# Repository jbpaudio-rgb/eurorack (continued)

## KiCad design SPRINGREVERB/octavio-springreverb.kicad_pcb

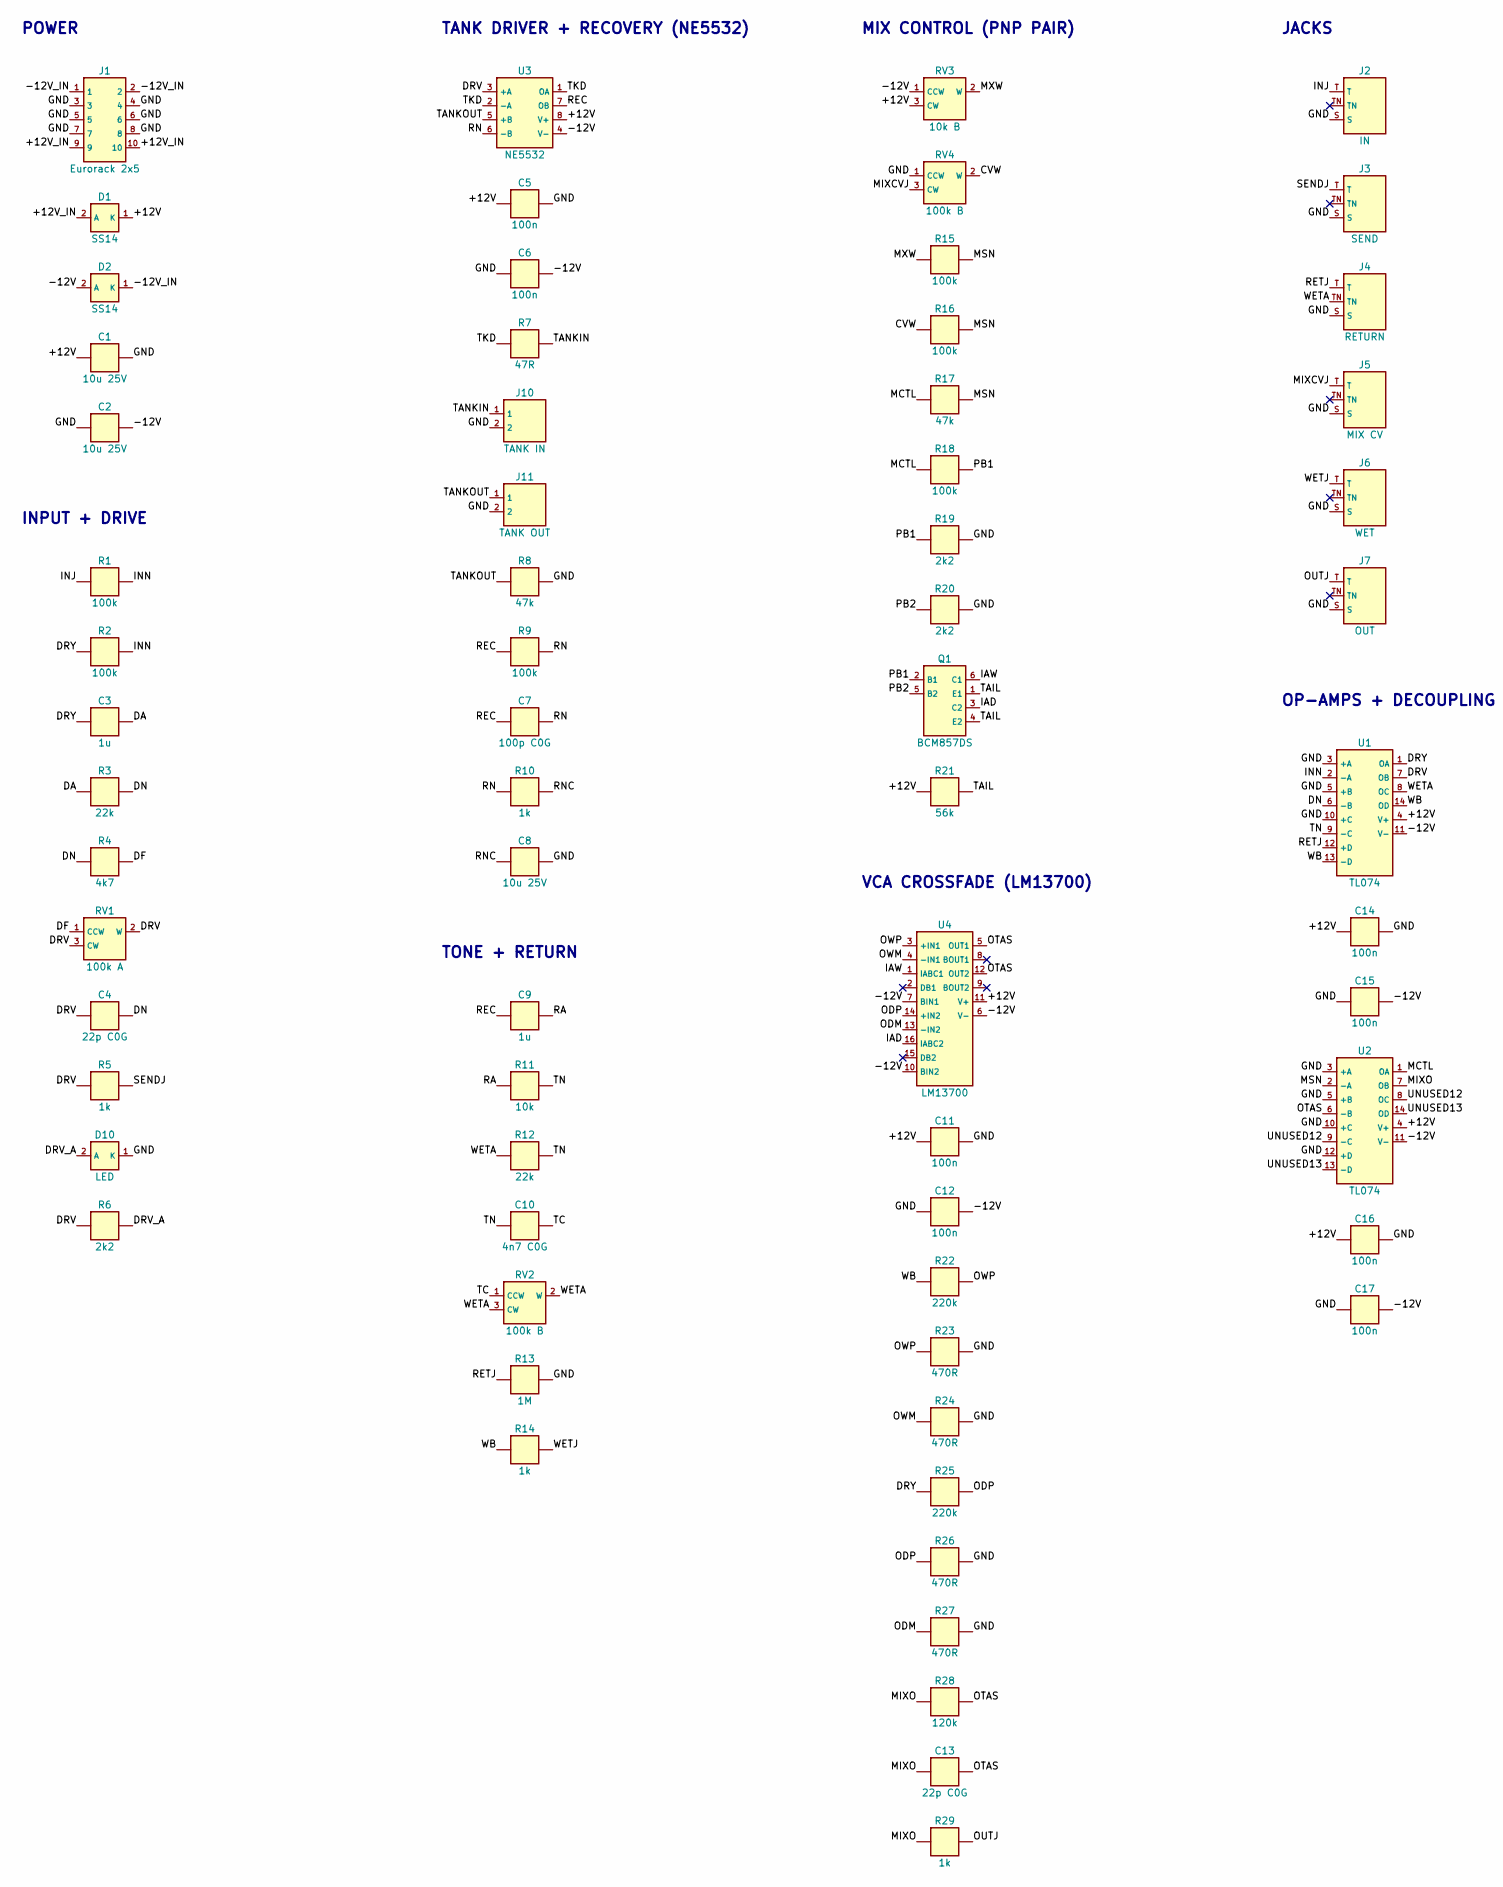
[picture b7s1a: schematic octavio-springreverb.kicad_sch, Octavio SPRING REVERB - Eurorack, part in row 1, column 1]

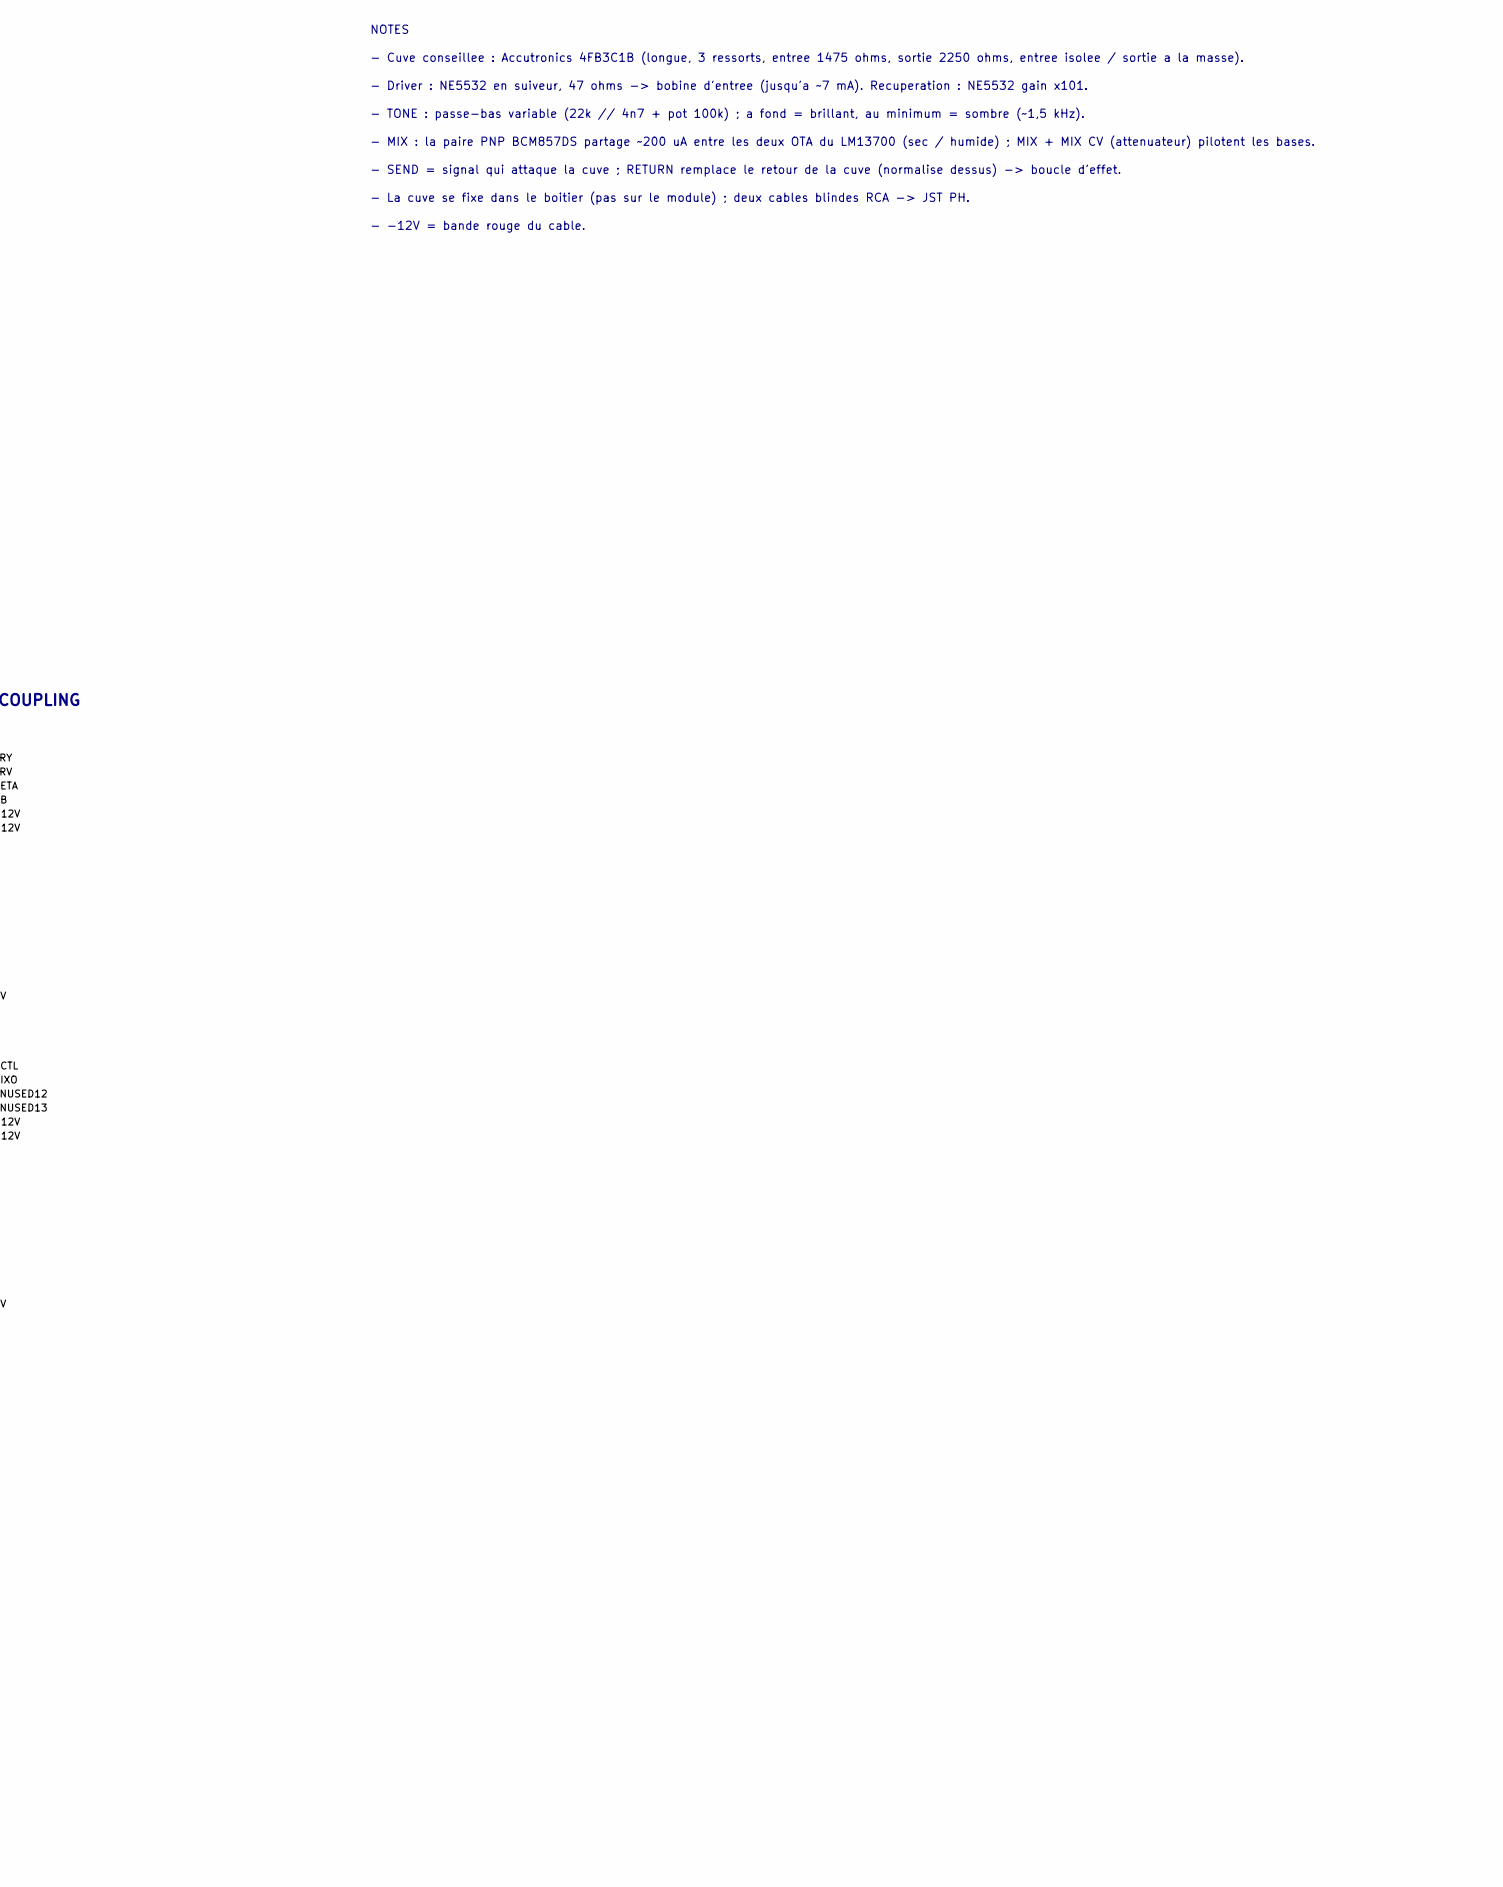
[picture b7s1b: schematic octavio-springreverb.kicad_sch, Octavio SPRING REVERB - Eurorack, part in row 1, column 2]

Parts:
C1, C2, C8: 10u 25V; C_1206_3216Metric; MPN X5R/X7R 1206
C3, C9: 1u; C_0603_1608Metric; MPN X7R 0603 25 V
C4, C13: 22p C0G; C_0603_1608Metric; MPN C0G/NP0 0603
C5, C6, C11, C12, C14, C15, C16, C17: 100n; C_0603_1608Metric
C7: 100p C0G; C_0603_1608Metric; MPN C0G/NP0 0603
C10: 4n7 C0G; C_0603_1608Metric; MPN C0G/NP0 0603
D1, D2: SS14; D_SMA; MPN SS14 (40 V 1 A Schottky)
D10: LED; LED_D3.0mm; MPN LED 3 mm rouge (PEAK : s'allume quand l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
J1: Eurorack 2x5; IDC-Header_2x05_P2.54mm_Vertical; MPN Shrouded header 2x5 2.54 mm
J2: IN; Jack_3.5mm_Thonkiconn_PJ398SM; MPN QingPu WQP-PJ301M-12 (Thonkiconn)
J3: SEND; Jack_3.5mm_Thonkiconn_PJ398SM; MPN QingPu WQP-PJ301M-12 (Thonkiconn)
J4: RETURN; Jack_3.5mm_Thonkiconn_PJ398SM; MPN QingPu WQP-PJ301M-12 (Thonkiconn)
J5: MIX CV; Jack_3.5mm_Thonkiconn_PJ398SM; MPN QingPu WQP-PJ301M-12 (Thonkiconn)
J6: WET; Jack_3.5mm_Thonkiconn_PJ398SM; MPN QingPu WQP-PJ301M-12 (Thonkiconn)
J7: OUT; Jack_3.5mm_Thonkiconn_PJ398SM; MPN QingPu WQP-PJ301M-12 (Thonkiconn)
J10: TANK IN; JST_PH_B2B-PH-K_1x02_P2.00mm_Vertical; MPN JST PH 2 broches (câble blindé vers la 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
J11: TANK OUT; JST_PH_B2B-PH-K_1x02_P2.00mm_Vertical; MPN JST PH 2 broches (câble blindé vers la 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
Q1: BCM857DS; SOT-457; MPN BCM857DS,115 (Nexperia, paire PNP appai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
R1, R2, R9, R15, R16, R18: 100k; R_0603_1608Metric
R3, R12: 22k; R_0603_1608Metric
R4: 4k7; R_0603_1608Metric
R5, R10, R14, R29: 1k; R_0603_1608Metric
R6, R19, R20: 2k2; R_0603_1608Metric
R7: 47R; R_0603_1608Metric
R8, R17: 47k; R_0603_1608Metric
R11: 10k; R_0603_1608Metric
R13: 1M; R_0603_1608Metric
R21: 56k; R_0603_1608Metric
R22, R25: 220k; R_0603_1608Metric
R23, R24, R26, R27: 470R; R_0603_1608Metric
R28: 120k; R_0603_1608Metric
RV1: 100k A; Pot_Alpha_9mm_Vertical; MPN POT-R09V-100K A (9 mm vertical, log)
RV2, RV4: 100k B; Pot_Alpha_9mm_Vertical; MPN POT-R09V-100K (9 mm vertical, B100k)
RV3: 10k B; Pot_Alpha_9mm_Vertical; MPN POT-R09V-10K B (9 mm vertical)
U1, U2: TL074; SOIC-14_3.9x8.7mm_P1.27mm; MPN TL074CDR
U3: NE5532; SOIC-8_3.9x4.9mm_P1.27mm; MPN NE5532DR (double ampli bas bruit, sorti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
U4: LM13700; SOIC-16_3.9x9.9mm_P1.27mm; MPN LM13700MX/NOPB

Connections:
+12V: C1.1, C5.1, C11.1, C14.1, C16.1, D1.1 (K), R21.1, RV3.3 (CW), U1.4 (V+), U2.4 (V+), U3.8 (V+), U4.11 (V+)
+12V_IN: D1.2 (A), J1.9, J1.10
-12V: C2.2, C6.2, C12.2, C15.2, C17.2, D2.2 (A), RV3.1 (CCW), U1.11 (V-), U2.11 (V-), U3.4 (V-), U4.6 (V-), U4.7 (BIN1), U4.10 (BIN2)
-12V_IN: D2.1 (K), J1.1, J1.2
CVW: R16.1, RV4.2 (W)
DA: C3.2, R3.1
DF: R4.2, RV1.1 (CCW)
DN: C4.2, R3.2, R4.1, U1.6 (-B)
DRV: C4.1, R5.1, R6.1, RV1.2 (W), RV1.3 (CW), U1.7 (OB), U3.3 (+A)
DRV_A: D10.2 (A), R6.2
DRY: C3.1, R2.1, R25.1, U1.1 (OA)
GND: C1.2, C2.1, C5.2, C6.1, C8.2, C11.2, C12.1, C14.2, C15.1, C16.2, C17.1, D10.1 (K), J1.3, J1.4, J1.5, J1.6, J1.7, J1.8, J2.S, J3.S, J4.S, J5.S, J6.S, J7.S, J10.2, J11.2, R8.2, R13.2, R19.2, R20.2, R23.2, R24.2, R26.2, R27.2, RV4.1 (CCW), U1.3 (+A), U1.5 (+B), U1.10 (+C), U2.3 (+A), U2.5 (+B), U2.10 (+C), U2.12 (+D)
IAD: Q1.3 (C2), U4.16 (IABC2)
IAW: Q1.6 (C1), U4.1 (IABC1)
INJ: J2.T, R1.1
INN: R1.2, R2.2, U1.2 (-A)
MCTL: R17.1, R18.1, U2.1 (OA)
MIXCVJ: J5.T, RV4.3 (CW)
MIXO: C13.1, R28.1, R29.1, U2.7 (OB)
MSN: R15.2, R16.2, R17.2, U2.2 (-A)
MXW: R15.1, RV3.2 (W)
ODM: R27.1, U4.13 (-IN2)
ODP: R25.2, R26.1, U4.14 (+IN2)
OTAS: C13.2, R28.2, U2.6 (-B), U4.5 (OUT1), U4.12 (OUT2)
OUTJ: J7.T, R29.2
OWM: R24.1, U4.4 (-IN1)
OWP: R22.2, R23.1, U4.3 (+IN1)
PB1: Q1.2 (B1), R18.2, R19.1
PB2: Q1.5 (B2), R20.1
RA: C9.2, R11.1
REC: C7.1, C9.1, R9.1, U3.7 (OB)
RETJ: J4.T, R13.1, U1.12 (+D)
RN: C7.2, R9.2, R10.1, U3.6 (-B)
RNC: C8.1, R10.2
SENDJ: J3.T, R5.2
TAIL: Q1.1 (E1), Q1.4 (E2), R21.2
TANKIN: J10.1, R7.2
TANKOUT: J11.1, R8.1, U3.5 (+B)
TC: C10.2, RV2.1 (CCW)
TKD: R7.1, U3.1 (OA), U3.2 (-A)
TN: C10.1, R11.2, R12.2, U1.9 (-C)
UNUSED12: U2.8 (OC), U2.9 (-C)
UNUSED13: U2.13 (-D), U2.14 (OD)
WB: R14.1, R22.1, U1.13 (-D), U1.14 (OD)
WETA: J4.TN, R12.1, RV2.2 (W), RV2.3 (CW), U1.8 (OC)
WETJ: J6.T, R14.2

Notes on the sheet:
POWER
INPUT + DRIVE
TANK DRIVER + RECOVERY (NE5532)
TONE + RETURN
MIX CONTROL (PNP PAIR)
VCA CROSSFADE (LM13700)
JACKS
OP-AMPS + DECOUPLING
NOTES
- Cuve conseillee : Accutronics 4FB3C1B (longue, 3 ressorts, entree 1475 ohms, sortie 2250 ohms, entree isolee / sortie a la masse).
- Driver : NE5532 en suiveur, 47 ohms -> bobine d'entree (jusqu'a ~7 mA). Recuperation : NE5532 gain x101.
- TONE : passe-bas variable (22k // 4n7 + pot 100k) ; a fond = brillant, au minimum = sombre (~1,5 kHz).
- MIX : la paire PNP BCM857DS partage ~200 uA entre les deux OTA du LM13700 (sec / humide) ; MIX + MIX CV (attenuateur) pilotent les bases.
- SEND = signal qui attaque la cuve ; RETURN remplace le retour de la cuve (normalise dessus) -> boucle d'effet.
- La cuve se fixe dans le boitier (pas sur le module) ; deux cables blindes RCA -> JST PH.
- -12V = bande rouge du cable.

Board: 2 copper layers, 67 parts (56 on the bottom side), 46 nets, no tracks yet.

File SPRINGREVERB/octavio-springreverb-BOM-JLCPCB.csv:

Comment,Designator,Footprint,LCSC Part #,Notes
10u 25V X5R/X7R 1206,"C1,C2,C8",C_1206_3216Metric,,X5R/X7R 1206 - SMT bottom - laisser JLC choisir (Basic de preference)
4n7 C0G C0G/NP0 0603,C10,C_0603_1608Metric,,C0G/NP0 0603 - SMT bottom - laisser JLC choisir (Basic de preference)
1u X7R 0603 25 V,"C3,C9",C_0603_1608Metric,,X7R 0603 25 V - SMT bottom - laisser JLC choisir (Basic de preference)
22p C0G C0G/NP0 0603,"C4,C13",C_0603_1608Metric,,C0G/NP0 0603 - SMT bottom - laisser JLC choisir (Basic de preference)
100n,"C5,C6,C11,C12,C14,C15,C16,C17",C_0603_1608Metric,,SMT bottom - laisser JLC choisir (Basic de preference)
100p C0G C0G/NP0 0603,C7,C_0603_1608Metric,,C0G/NP0 0603 - SMT bottom - laisser JLC choisir (Basic de preference)
SS14,"D1,D2",D_SMA,,SS14 (40 V 1 A Schottky) - SMT bottom - laisser JLC choisir (Basic de preference)
LED,D10,LED_D3.0mm,,LED 3 mm rouge (PEAK : s'allume quand les ressorts sont bien attaqués) - THT (wave soldering) - laisser JLC choisir (Basic de preference)
Eurorack 2x5,J1,IDC-Header_2x05_P2.54mm_Vertical,,Shrouded header 2x5 2.54 mm - THT (wave soldering) - laisser JLC choisir (Basic de preference)
TANK IN,J10,JST_PH_B2B-PH-K_1x02_P2.00mm_Vertical,,JST PH 2 broches (câble blindé vers la fiche RCA IN de la cuve) - THT (wave soldering) - laisser JLC choisir (Basic de preference)
TANK OUT,J11,JST_PH_B2B-PH-K_1x02_P2.00mm_Vertical,,JST PH 2 broches (câble blindé vers la fiche RCA OUT de la cuve) - THT (wave soldering) - laisser JLC choisir (Basic de preference)
IN,J2,Jack_3.5mm_Thonkiconn_PJ398SM,C9900080080,QingPu WQP-PJ301M-12 (Thonkiconn) - THT (wave soldering)
SEND,J3,Jack_3.5mm_Thonkiconn_PJ398SM,C9900080080,QingPu WQP-PJ301M-12 (Thonkiconn) - THT (wave soldering)
RETURN,J4,Jack_3.5mm_Thonkiconn_PJ398SM,C9900080080,QingPu WQP-PJ301M-12 (Thonkiconn) - THT (wave soldering)
MIX CV,J5,Jack_3.5mm_Thonkiconn_PJ398SM,C9900080080,QingPu WQP-PJ301M-12 (Thonkiconn) - THT (wave soldering)
WET,J6,Jack_3.5mm_Thonkiconn_PJ398SM,C9900080080,QingPu WQP-PJ301M-12 (Thonkiconn) - THT (wave soldering)
OUT,J7,Jack_3.5mm_Thonkiconn_PJ398SM,C9900080080,QingPu WQP-PJ301M-12 (Thonkiconn) - THT (wave soldering)
"BCM857DS,115",Q1,SOT-457,,"BCM857DS,115 (Nexperia, paire PNP appairée) - SMT bottom - laisser JLC choisir (Basic de preference)"
100k 1% 0805,"R1,R2,R9,R15,R16,R18",R_0603_1608Metric,,SMT bottom - laisser JLC choisir (Basic de preference)
10k 1% 0805,R11,R_0603_1608Metric,,SMT bottom - laisser JLC choisir (Basic de preference)
1M 1% 0805,R13,R_0603_1608Metric,,SMT bottom - laisser JLC choisir (Basic de preference)
56k 1% 0805,R21,R_0603_1608Metric,,SMT bottom - laisser JLC choisir (Basic de preference)
220k 1% 0805,"R22,R25",R_0603_1608Metric,,SMT bottom - laisser JLC choisir (Basic de preference)
470R 1% 0805,"R23,R24,R26,R27",R_0603_1608Metric,,SMT bottom - laisser JLC choisir (Basic de preference)
120k 1% 0805,R28,R_0603_1608Metric,,SMT bottom - laisser JLC choisir (Basic de preference)
22k 1% 0805,"R3,R12",R_0603_1608Metric,,SMT bottom - laisser JLC choisir (Basic de preference)
4k7 1% 0805,R4,R_0603_1608Metric,,SMT bottom - laisser JLC choisir (Basic de preference)
1k 1% 0805,"R5,R10,R14,R29",R_0603_1608Metric,,SMT bottom - laisser JLC choisir (Basic de preference)
2k2 1% 0805,"R6,R19,R20",R_0603_1608Metric,,SMT bottom - laisser JLC choisir (Basic de preference)
47R 1% 0805,R7,R_0603_1608Metric,,SMT bottom - laisser JLC choisir (Basic de preference)
47k 1% 0805,"R8,R17",R_0603_1608Metric,,SMT bottom - laisser JLC choisir (Basic de preference)
100k A,RV1,Pot_Alpha_9mm_Vertical,,"POT-R09V-100K A (9 mm vertical, log) - THT (wave soldering) - laisser JLC choisir (Basic de preference)"
100k B,"RV2,RV4",Pot_Alpha_9mm_Vertical,C9900018037,"POT-R09V-100K (9 mm vertical, B100k) - THT (wave soldering)"
10k B,RV3,Pot_Alpha_9mm_Vertical,,POT-R09V-10K B (9 mm vertical) - THT (wave soldering) - laisser JLC choisir (Basic de preference)
TL074CDR,"U1,U2",SOIC-14_3.9x8.7mm_P1.27mm,C12594,TL074CDR - SMT bottom
NE5532DR,U3,SOIC-8_3.9x4.9mm_P1.27mm,,"NE5532DR (double ampli bas bruit, sortie 30 mA) - SMT bottom - laisser JLC choisir (Basic de preference)"
LM13700MX/NOPB,U4,SOIC-16_3.9x9.9mm_P1.27mm,,LM13700MX/NOPB - SMT bottom - laisser JLC choisir (Basic de preference)

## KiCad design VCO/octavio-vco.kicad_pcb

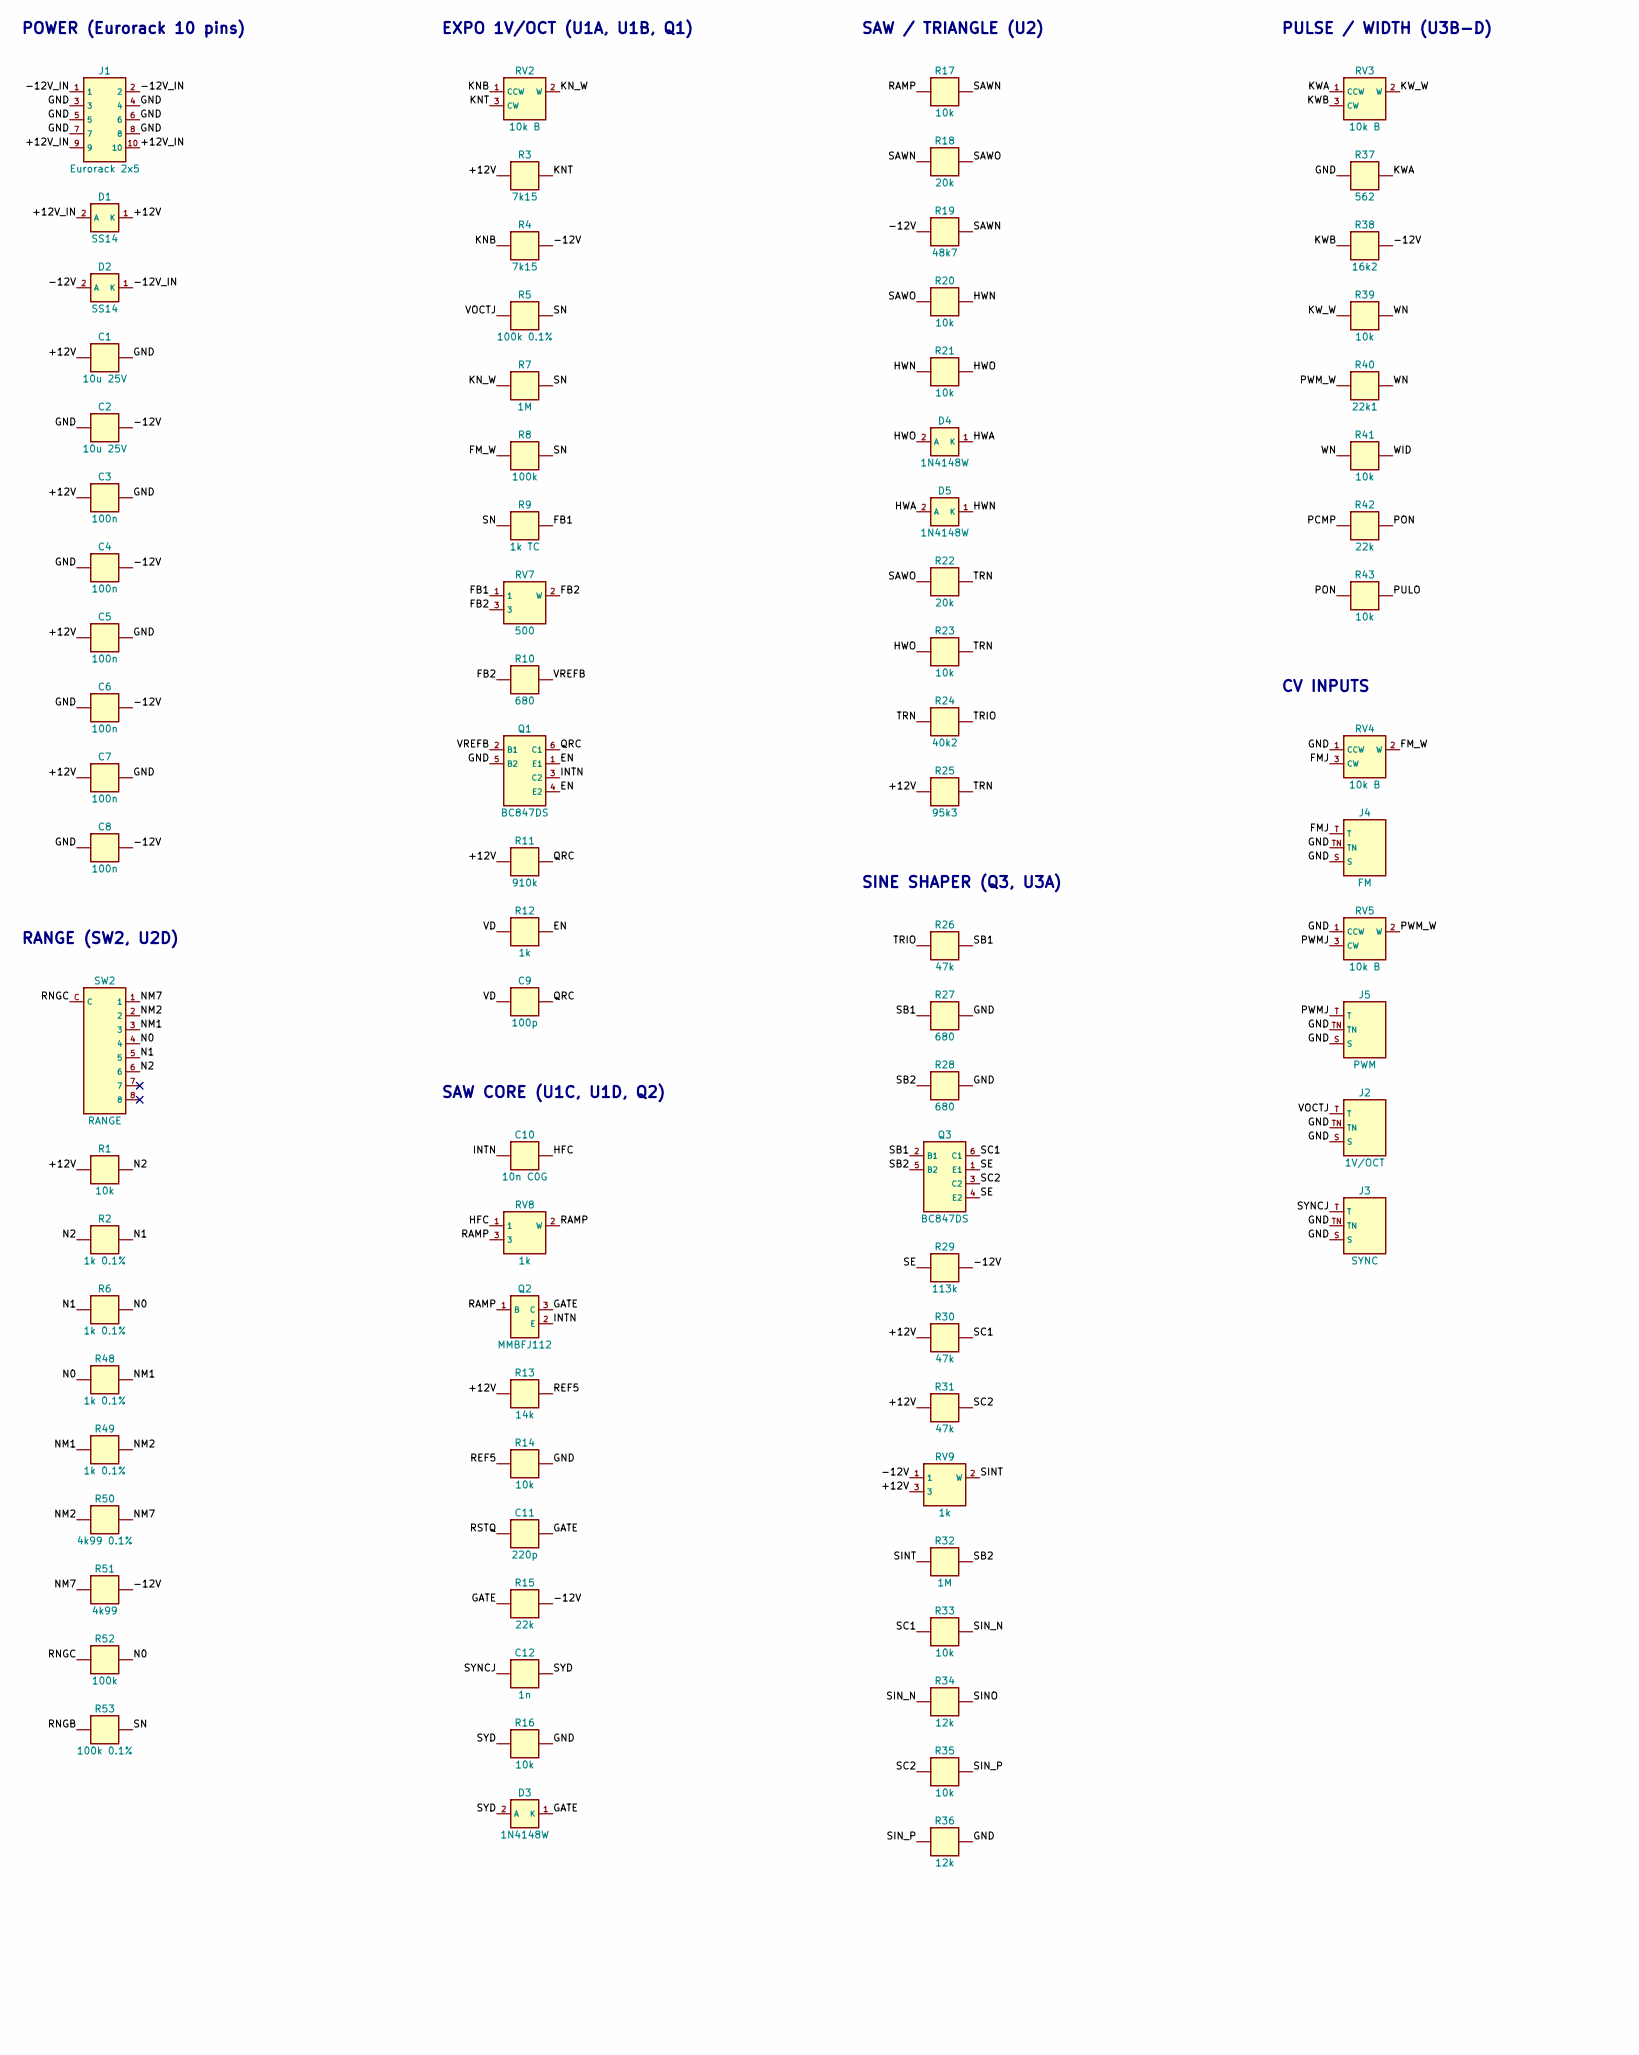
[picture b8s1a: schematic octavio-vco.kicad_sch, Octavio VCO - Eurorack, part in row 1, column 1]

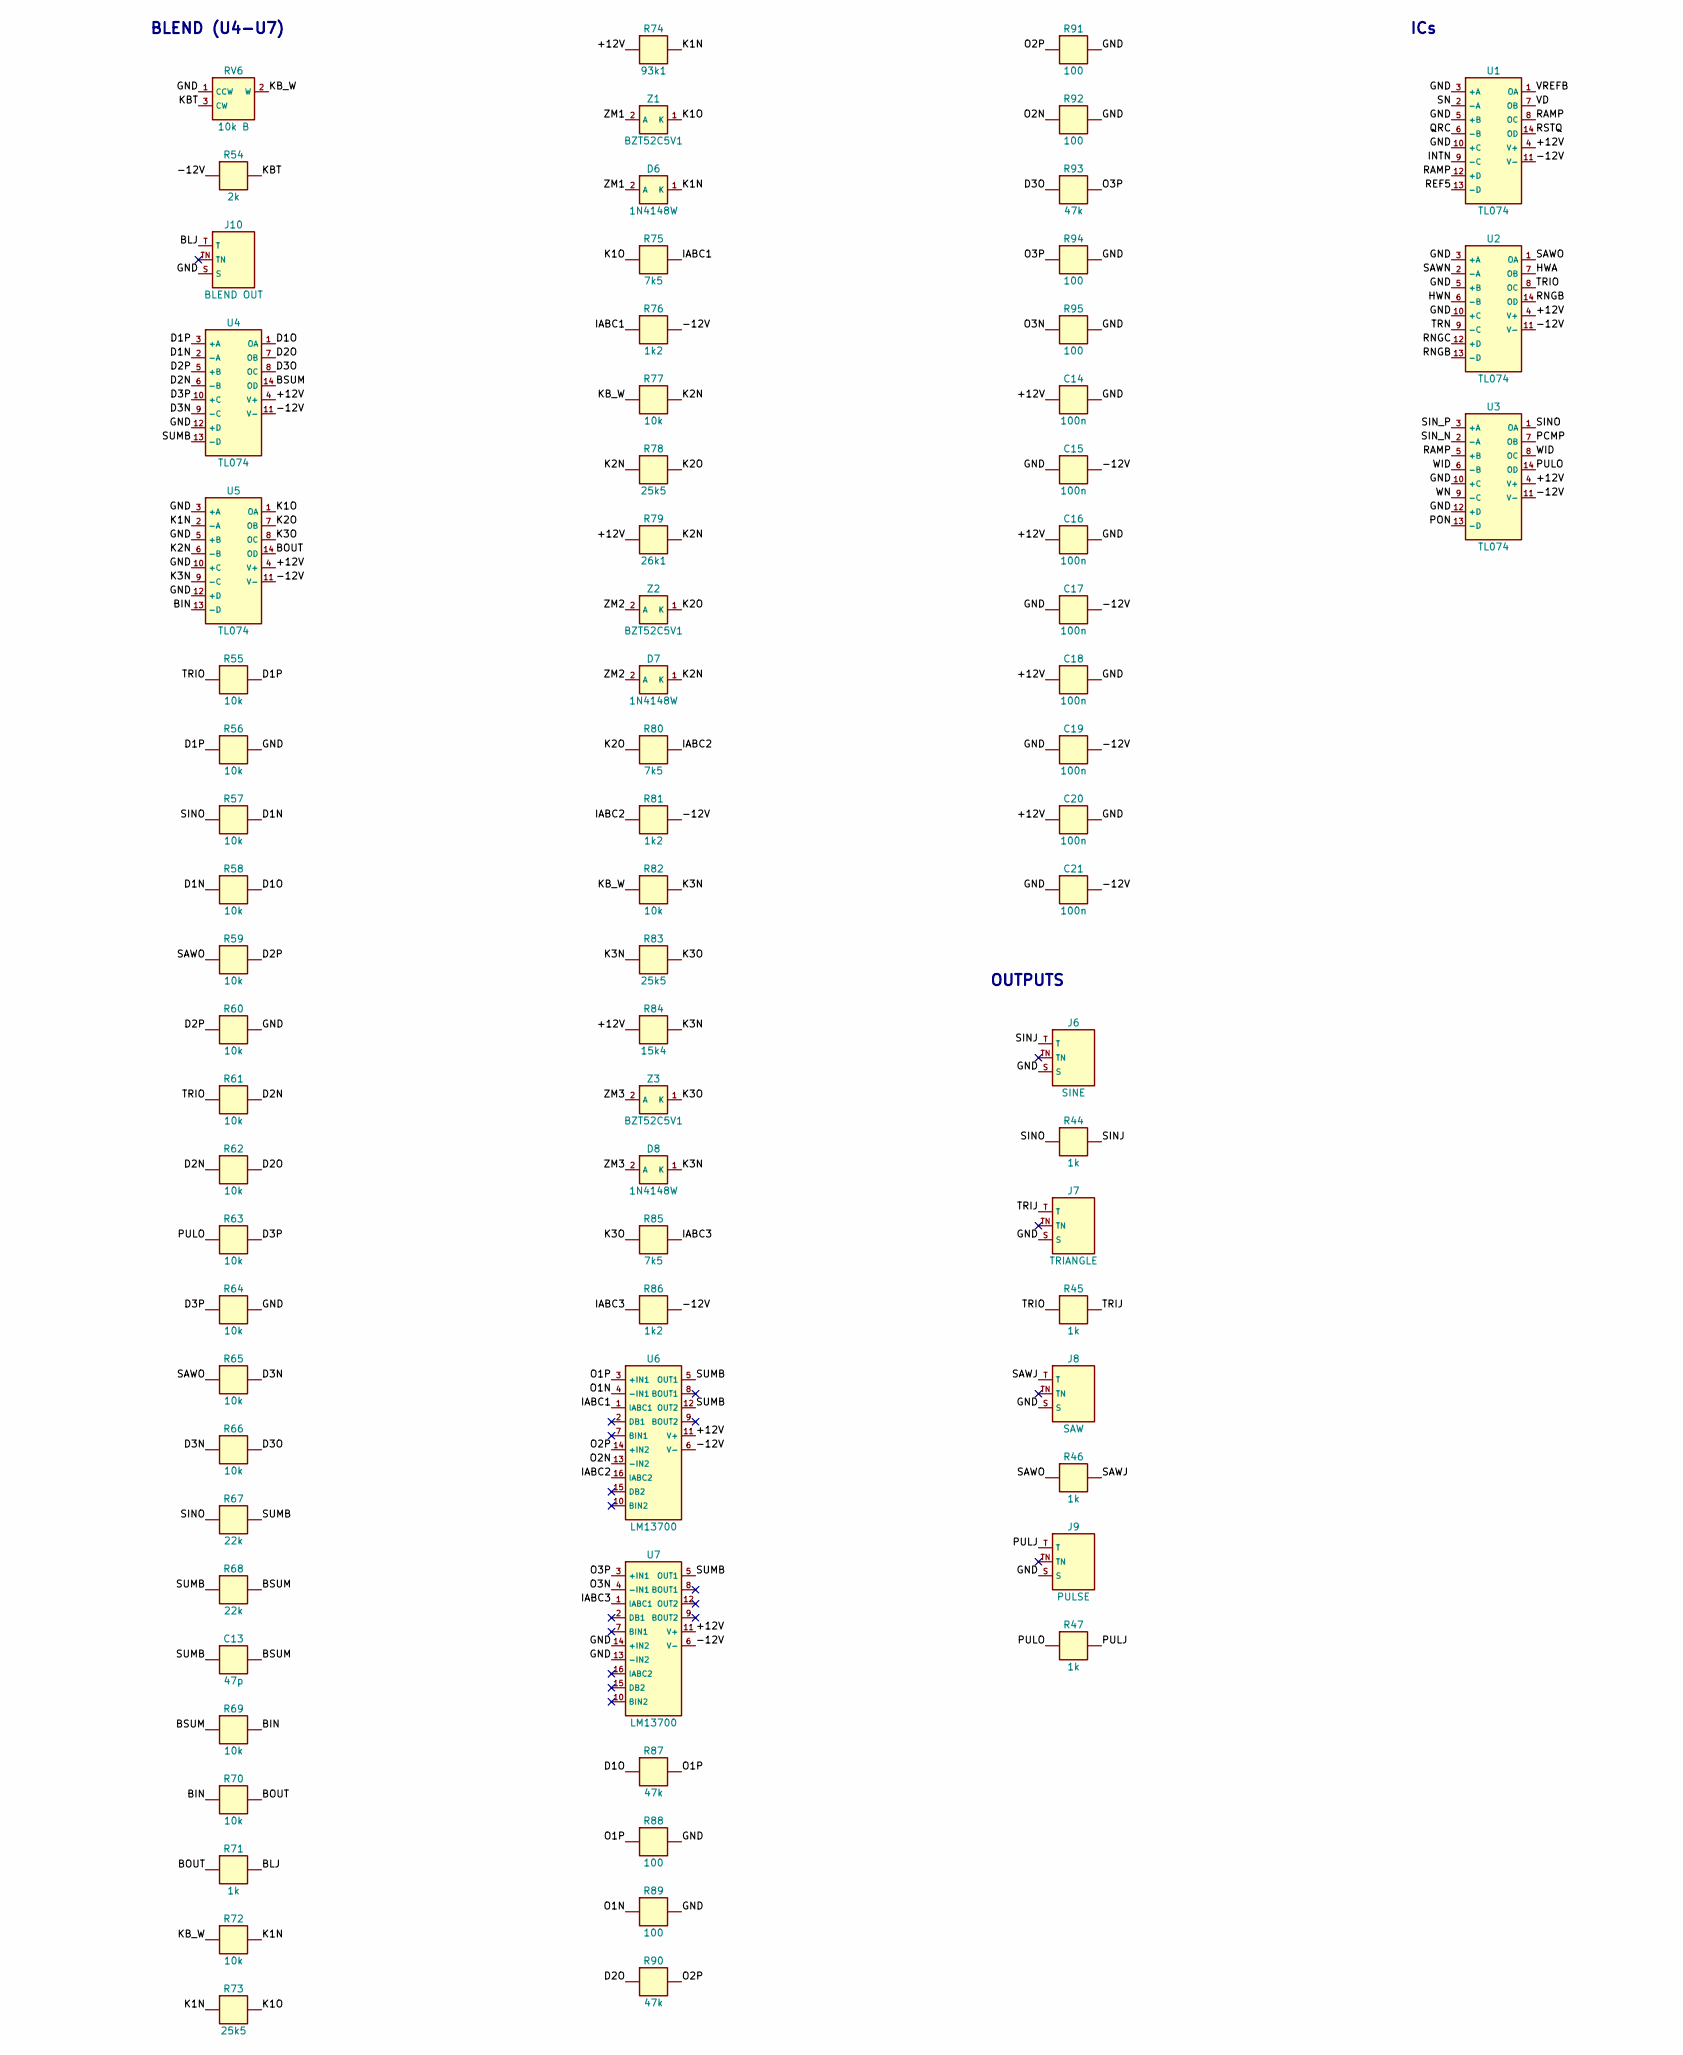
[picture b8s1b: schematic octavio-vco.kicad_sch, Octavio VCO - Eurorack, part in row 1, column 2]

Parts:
C1, C2: 10u 25V; C_1206_3216Metric; MPN X5R/X7R 1206
C3, C4, C5, C6, C7, C8, C14, C15, C16, C17, C18, C19, C20, C21: 100n; C_0603_1608Metric
C9: 100p; C_0603_1608Metric
C10: 10n C0G; C_1206_3216Metric; MPN 10 nF C0G/NP0 1206 (condensateur de tim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
C11: 220p; C_0603_1608Metric
C12: 1n; C_0603_1608Metric
C13: 47p; C_0603_1608Metric
D1, D2: SS14; D_SMA; MPN SS14 (40 V 1 A Schottky)
D3, D4, D5, D6, D7, D8: 1N4148W; D_SOD-123; MPN 1N4148W
J1: Eurorack 2x5; IDC-Header_2x05_P2.54mm_Vertical; MPN Shrouded header 2x5 2.54 mm
J2: 1V/OCT; Jack_3.5mm_Thonkiconn_PJ398SM; MPN QingPu WQP-PJ301M-12 (Thonkiconn)
J3: SYNC; Jack_3.5mm_Thonkiconn_PJ398SM; MPN QingPu WQP-PJ301M-12 (Thonkiconn)
J4: FM; Jack_3.5mm_Thonkiconn_PJ398SM; MPN QingPu WQP-PJ301M-12 (Thonkiconn)
J5: PWM; Jack_3.5mm_Thonkiconn_PJ398SM; MPN QingPu WQP-PJ301M-12 (Thonkiconn)
J6: SINE; Jack_3.5mm_Thonkiconn_PJ398SM; MPN QingPu WQP-PJ301M-12 (Thonkiconn)
J7: TRIANGLE; Jack_3.5mm_Thonkiconn_PJ398SM; MPN QingPu WQP-PJ301M-12 (Thonkiconn)
J8: SAW; Jack_3.5mm_Thonkiconn_PJ398SM; MPN QingPu WQP-PJ301M-12 (Thonkiconn)
J9: PULSE; Jack_3.5mm_Thonkiconn_PJ398SM; MPN QingPu WQP-PJ301M-12 (Thonkiconn)
J10: BLEND OUT; Jack_3.5mm_Thonkiconn_PJ398SM; MPN QingPu WQP-PJ301M-12 (Thonkiconn)
Q1, Q3: BC847DS; SOT-457; MPN BC847DS,115 (Nexperia, paire double)
Q2: MMBFJ112; SOT-23; MPN MMBFJ112 (JFET N, D-S-G)
R1, R14, R16, R17, R20, R21, R23, R33, R35, R39, R41, R43, R55, R56, R57, R58, R59, R60, R61, R62, R63, R64, R65, R66, R69, R70, R72, R77, R82: 10k; R_0603_1608Metric
R2, R6, R48, R49: 1k 0.1%; R_0603_1608Metric; MPN 1k 0,1 % 25 ppm
R3, R4: 7k15; R_0603_1608Metric
R5: 100k 0.1%; R_0603_1608Metric; MPN 100k 0,1 % 25 ppm (précision 1 V/oct)
R7, R32: 1M; R_0603_1608Metric
R8, R52: 100k; R_0603_1608Metric
R9: 1k TC; R_0603_1608Metric; MPN 1k +3300 ppm/K (thermistance de compens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
R10, R27, R28: 680; R_0603_1608Metric
R11: 910k; R_0603_1608Metric
R12, R44, R45, R46, R47, R71: 1k; R_0603_1608Metric
R13: 14k; R_0603_1608Metric
R15, R42, R67, R68: 22k; R_0603_1608Metric
R18, R22: 20k; R_0603_1608Metric
R19: 48k7; R_0603_1608Metric
R24: 40k2; R_0603_1608Metric
R25: 95k3; R_0603_1608Metric
R26, R30, R31, R87, R90, R93: 47k; R_0603_1608Metric
R29: 113k; R_0603_1608Metric
R34, R36: 12k; R_0603_1608Metric
R37: 562; R_0603_1608Metric
R38: 16k2; R_0603_1608Metric
R40: 22k1; R_0603_1608Metric
R50: 4k99 0.1%; R_0603_1608Metric; MPN 4k99 0,1 % 25 ppm
R51: 4k99; R_0603_1608Metric
R53: 100k 0.1%; R_0603_1608Metric; MPN 100k 0,1 % 25 ppm
R54: 2k; R_0603_1608Metric
R73, R78, R83: 25k5; R_0603_1608Metric
R74: 93k1; R_0603_1608Metric
R75, R80, R85: 7k5; R_0603_1608Metric
R76, R81, R86: 1k2; R_0603_1608Metric
R79: 26k1; R_0603_1608Metric
R84: 15k4; R_0603_1608Metric
R88, R89, R91, R92, R94, R95: 100; R_0603_1608Metric
RV2, RV3, RV4, RV5, RV6: 10k B; Pot_Alpha_9mm_Vertical; MPN POT-R09V-10K (9 mm vertical, B10k)
RV7: 500; Trim_SMD_Bourns_3314J; MPN Bourns 3314J-1-501E (trimmer CMS, régla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
RV8: 1k; Trim_SMD_Bourns_3314J; MPN Bourns 3314J-1-102E (trimmer CMS, régla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
RV9: 1k; Trim_SMD_Bourns_3314J; MPN Bourns 3314J-1-102E (trimmer CMS, symét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
SW2: RANGE; Rotary_SR16_1P8T; MPN Mini commutateur rotatif SR16 1 circuit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
U1, U2, U3, U4, U5: TL074; SOIC-14_3.9x8.7mm_P1.27mm; MPN TL074CDR
U6, U7: LM13700; SOIC-16_3.9x9.9mm_P1.27mm; MPN LM13700MX/NOPB
Z1, Z2, Z3: BZT52C5V1; D_SOD-123; MPN BZT52C5V1 (zener 5,1 V)

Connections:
+12V: C1.1, C3.1, C5.1, C7.1, C14.1, C16.1, C18.1, C20.1, D1.1 (K), R1.1, R3.1, R11.1, R13.1, R25.1, R30.1, R31.1, R74.1, R79.1, R84.1, RV9.3, U1.4 (V+), U2.4 (V+), U3.4 (V+), U4.4 (V+), U5.4 (V+), U6.11 (V+), U7.11 (V+)
+12V_IN: D1.2 (A), J1.9, J1.10
-12V: C2.2, C4.2, C6.2, C8.2, C15.2, C17.2, C19.2, C21.2, D2.2 (A), R4.2, R15.2, R19.1, R29.2, R38.2, R51.2, R54.1, R76.2, R81.2, R86.2, RV9.1, U1.11 (V-), U2.11 (V-), U3.11 (V-), U4.11 (V-), U5.11 (V-), U6.6 (V-), U7.6 (V-)
-12V_IN: D2.1 (K), J1.1, J1.2
BIN: R69.2, R70.1, U5.13 (-D)
BLJ: J10.T, R71.2
BOUT: R70.2, R71.1, U5.14 (OD)
BSUM: C13.2, R68.2, R69.1, U4.14 (OD)
D1N: R57.2, R58.1, U4.2 (-A)
D1O: R58.2, R87.1, U4.1 (OA)
D1P: R55.2, R56.1, U4.3 (+A)
D2N: R61.2, R62.1, U4.6 (-B)
D2O: R62.2, R90.1, U4.7 (OB)
D2P: R59.2, R60.1, U4.5 (+B)
D3N: R65.2, R66.1, U4.9 (-C)
D3O: R66.2, R93.1, U4.8 (OC)
D3P: R63.2, R64.1, U4.10 (+C)
EN: Q1.1 (E1), Q1.4 (E2), R12.2
FB1: R9.2, RV7.1
FB2: R10.1, RV7.2 (W), RV7.3
FMJ: J4.T, RV4.3 (CW)
FM_W: R8.1, RV4.2 (W)
GATE: C11.2, D3.1 (K), Q2.3 (C), R15.1
GND: C1.2, C2.1, C3.2, C4.1, C5.2, C6.1, C7.2, C8.1, C14.2, C15.1, C16.2, C17.1, C18.2, C19.1, C20.2, C21.1, J1.3, J1.4, J1.5, J1.6, J1.7, J1.8, J2.S, J2.TN, J3.S, J3.TN, J4.S, J4.TN, J5.S, J5.TN, J6.S, J7.S, J8.S, J9.S, J10.S, Q1.5 (B2), R14.2, R16.2, R27.2, R28.2, R36.2, R37.1, R56.2, R60.2, R64.2, R88.2, R89.2, R91.2, R92.2, R94.2, R95.2, RV4.1 (CCW), RV5.1 (CCW), RV6.1 (CCW), U1.3 (+A), U1.5 (+B), U1.10 (+C), U2.3 (+A), U2.5 (+B), U2.10 (+C), U3.10 (+C), U3.12 (+D), U4.12 (+D), U5.3 (+A), U5.5 (+B), U5.10 (+C), U5.12 (+D), U7.13 (-IN2), U7.14 (+IN2)
HFC: C10.2, RV8.1
HWA: D4.1 (K), D5.2 (A), U2.7 (OB)
HWN: D5.1 (K), R20.2, R21.1, U2.6 (-B)
HWO: D4.2 (A), R21.2, R23.1
IABC1: R75.2, R76.1, U6.1 (IABC1)
IABC2: R80.2, R81.1, U6.16 (IABC2)
IABC3: R85.2, R86.1, U7.1 (IABC1)
INTN: C10.1, Q1.3 (C2), Q2.2 (E), U1.9 (-C)
K1N: D6.1 (K), R72.2, R73.1, R74.2, U5.2 (-A)
K1O: R73.2, R75.1, U5.1 (OA), Z1.1 (K)
K2N: D7.1 (K), R77.2, R78.1, R79.2, U5.6 (-B)
K2O: R78.2, R80.1, U5.7 (OB), Z2.1 (K)
K3N: D8.1 (K), R82.2, R83.1, R84.2, U5.9 (-C)
K3O: R83.2, R85.1, U5.8 (OC), Z3.1 (K)
KBT: R54.2, RV6.3 (CW)
KB_W: R72.1, R77.1, R82.1, RV6.2 (W)
KNB: R4.1, RV2.1 (CCW)
KNT: R3.2, RV2.3 (CW)
KN_W: R7.1, RV2.2 (W)
KWA: R37.2, RV3.1 (CCW)
KWB: R38.1, RV3.3 (CW)
KW_W: R39.1, RV3.2 (W)
N0: R6.2, R48.1, R52.2, SW2.4
N1: R2.2, R6.1, SW2.5
N2: R1.2, R2.1, SW2.6
NM1: R48.2, R49.1, SW2.3
NM2: R49.2, R50.1, SW2.2
NM7: R50.2, R51.1, SW2.1
O1N: R89.1, U6.4 (-IN1)
O1P: R87.2, R88.1, U6.3 (+IN1)
O2N: R92.1, U6.13 (-IN2)
O2P: R90.2, R91.1, U6.14 (+IN2)
O3N: R95.1, U7.4 (-IN1)
O3P: R93.2, R94.1, U7.3 (+IN1)
PCMP: R42.1, U3.7 (OB)
PON: R42.2, R43.1, U3.13 (-D)
PULJ: J9.T, R47.2
PULO: R43.2, R47.1, R63.1, U3.14 (OD)
PWMJ: J5.T, RV5.3 (CW)
PWM_W: R40.1, RV5.2 (W)
QRC: C9.2, Q1.6 (C1), R11.2, U1.6 (-B)
RAMP: Q2.1 (B), R17.1, RV8.2 (W), RV8.3, U1.8 (OC), U1.12 (+D), U3.5 (+B)
REF5: R13.2, R14.1, U1.13 (-D)
RNGB: R53.1, U2.13 (-D), U2.14 (OD)
RNGC: R52.1, SW2.C, U2.12 (+D)
RSTQ: C11.1, U1.14 (OD)
SAWJ: J8.T, R46.2
SAWN: R17.2, R18.1, R19.2, U2.2 (-A)
SAWO: R18.2, R20.1, R22.1, R46.1, R59.1, R65.1, U2.1 (OA)
SB1: Q3.2 (B1), R26.2, R27.1
SB2: Q3.5 (B2), R28.1, R32.2
SC1: Q3.6 (C1), R30.2, R33.1
SC2: Q3.3 (C2), R31.2, R35.1
SE: Q3.1 (E1), Q3.4 (E2), R29.1
SINJ: J6.T, R44.2
SINO: R34.2, R44.1, R57.1, R67.1, U3.1 (OA)
SINT: R32.1, RV9.2 (W)
SIN_N: R33.2, R34.1, U3.2 (-A)
SIN_P: R35.2, R36.1, U3.3 (+A)
SN: R5.2, R7.2, R8.2, R9.1, R53.2, U1.2 (-A)
SUMB: C13.1, R67.2, R68.1, U4.13 (-D), U6.5 (OUT1), U6.12 (OUT2), U7.5 (OUT1)
SYD: C12.2, D3.2 (A), R16.1
SYNCJ: C12.1, J3.T
TRIJ: J7.T, R45.2
TRIO: R24.2, R26.1, R45.1, R55.1, R61.1, U2.8 (OC)
TRN: R22.2, R23.2, R24.1, R25.2, U2.9 (-C)
VD: C9.1, R12.1, U1.7 (OB)
VOCTJ: J2.T, R5.1
VREFB: Q1.2 (B1), R10.2, U1.1 (OA)
WID: R41.2, U3.6 (-B), U3.8 (OC)
WN: R39.2, R40.2, R41.1, U3.9 (-C)
ZM1: D6.2 (A), Z1.2 (A)
ZM2: D7.2 (A), Z2.2 (A)
ZM3: D8.2 (A), Z3.2 (A)

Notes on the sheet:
POWER (Eurorack 10 pins)
RANGE (SW2, U2D)
EXPO 1V/OCT (U1A, U1B, Q1)
SAW CORE (U1C, U1D, Q2)
SAW / TRIANGLE (U2)
SINE SHAPER (Q3, U3A)
PULSE / WIDTH (U3B-D)
CV INPUTS
BLEND (U4-U7)
OUTPUTS
ICs
NOTES
- RANGE (SW2, mini SR16 1P8T, butee sur 6) : LO, 32', 16', 8', 4', 2' = -7, -2, -1, 0, +1, +2 octaves (echelle 0,1 %, tampon U2D). FREQUENCY = +/- 6 demi-tons.
- Coeur dent de scie facon 921 : convertisseur expo (Q1, U1A/U1B) -> integrateur U1C (C10 10 nF) -> remise a zero par JFET Q2 quand la rampe atteint 5 V (U1D).
- 1V/OCT : R5 100k 0,1 %, R9 1k +3300 ppm colle a Q1, reglage RV7 ; aigus : RV8 en serie avec C10.
- Formes : SAW (U2A), TRIANGLE (redresseur double alternance U2B/U2C), SINE (paire Q3 + U3A, symetrie RV9), PULSE (U3B, largeur U3C).
- BLEND : SINE -> TRIANGLE -> SAW -> PULSE en continu (differences U4, 3 OTA U6/U7, commandes U5 avec zeners de butee).
- SYNC : front montant -> impulsion sur la grille de Q2 (synchro dure).
- -12V = bande rouge du cable.

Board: 2 copper layers, 156 parts (141 on the bottom side), 98 nets, no tracks yet.
